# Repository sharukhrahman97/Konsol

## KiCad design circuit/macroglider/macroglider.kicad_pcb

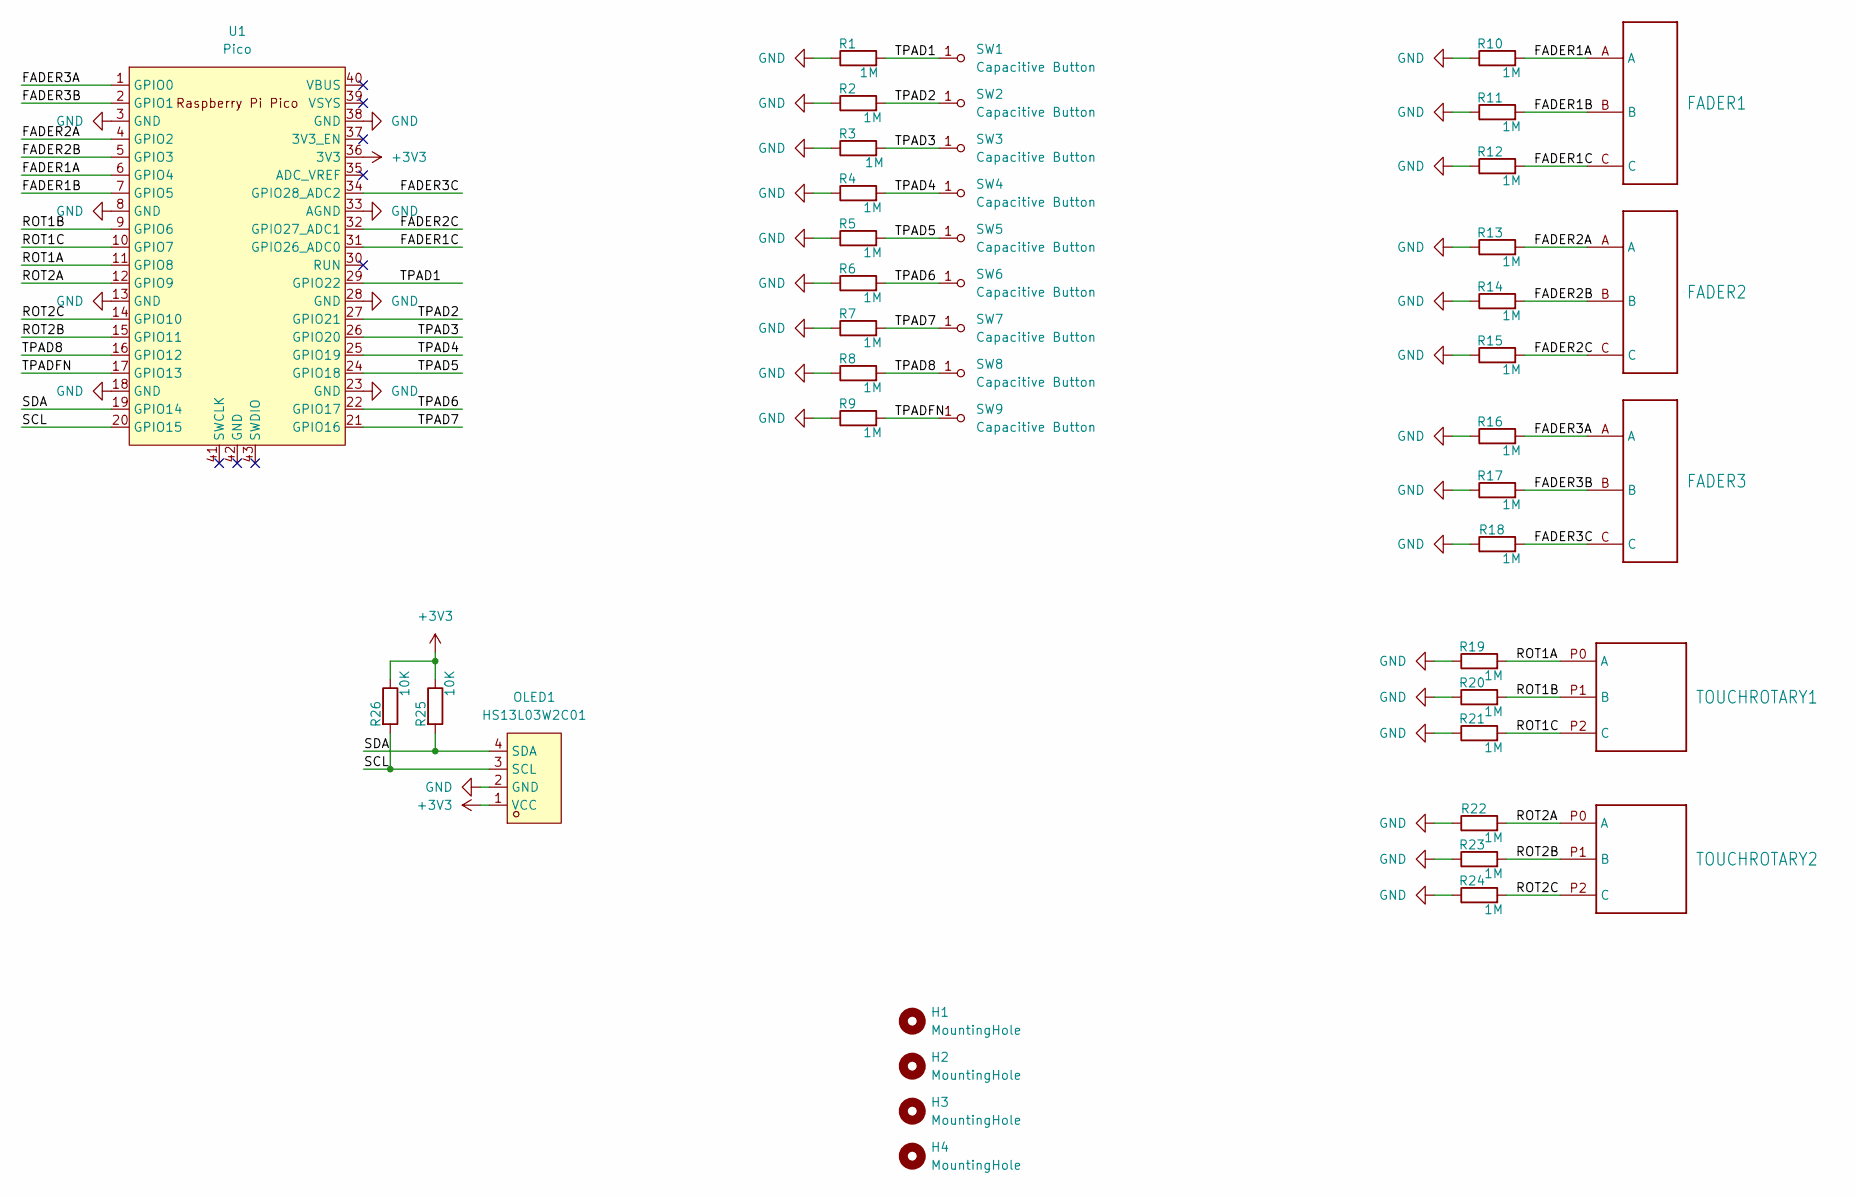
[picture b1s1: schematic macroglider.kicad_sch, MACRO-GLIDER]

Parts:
FADER1, FADER2, FADER3: TOUCHSLIDER3_8x40B
H1, H2, H3, H4: MountingHole; MountingHole_2.7mm_M2.5_ISO14580
OLED1: HS13L03W2C01; OLED-TH_L35.4-W33.5_HS13L03W2C01_without_mount_outline; LCSC Part C7465997
R1, R2, R3, R4, R5, R6, R7, R8, R9, R10, R11, R12, R13, R14, R15, R16, R17, R18, R19, R20, R21, R22, R23, R24: 1M; R_0603_1608Metric
R25, R26: 10K; R_0603_1608Metric
SW1, SW2, SW3, SW4, SW5, SW6, SW7, SW8, SW9: Capacitive Button; Pad-CapacitiveTouch
TOUCHROTARY1, TOUCHROTARY2: TOUCHROTARY1B
U1: Pico; RPi_Pico_SMD

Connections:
+3V3: OLED1.1 (VCC), R25.1, R26.1, U1.36 (3V3)
/FADER1A: FADER1.A, R10.2, U1.6 (GPIO4)
/FADER1B: FADER1.B, R11.2, U1.7 (GPIO5)
/FADER1C: FADER1.C, R12.2, U1.31 (GPIO26_ADC0)
/FADER2A: FADER2.A, R13.2, U1.4 (GPIO2)
/FADER2B: FADER2.B, R14.2, U1.5 (GPIO3)
/FADER2C: FADER2.C, R15.2, U1.32 (GPIO27_ADC1)
/FADER3A: FADER3.A, R16.2, U1.1 (GPIO0)
/FADER3B: FADER3.B, R17.2, U1.2 (GPIO1)
/FADER3C: FADER3.C, R18.2, U1.34 (GPIO28_ADC2)
/ROT1A: R19.2, TOUCHROTARY1.P0 (A), U1.11 (GPIO8)
/ROT1B: R20.2, TOUCHROTARY1.P1 (B), U1.9 (GPIO6)
/ROT1C: R21.2, TOUCHROTARY1.P2 (C), U1.10 (GPIO7)
/ROT2A: R22.2, TOUCHROTARY2.P0 (A), U1.12 (GPIO9)
/ROT2B: R23.2, TOUCHROTARY2.P1 (B), U1.15 (GPIO11)
/ROT2C: R24.2, TOUCHROTARY2.P2 (C), U1.14 (GPIO10)
/SCL: OLED1.3 (SCL), R26.2, U1.20 (GPIO15)
/SDA: OLED1.4 (SDA), R25.2, U1.19 (GPIO14)
/TPAD1: R1.2, SW1.1 (A), U1.29 (GPIO22)
/TPAD2: R2.2, SW2.1 (A), U1.27 (GPIO21)
/TPAD3: R3.2, SW3.1 (A), U1.26 (GPIO20)
/TPAD4: R4.2, SW4.1 (A), U1.25 (GPIO19)
/TPAD5: R5.2, SW5.1 (A), U1.24 (GPIO18)
/TPAD6: R6.2, SW6.1 (A), U1.22 (GPIO17)
/TPAD7: R7.2, SW7.1 (A), U1.21 (GPIO16)
/TPAD8: R8.2, SW8.1 (A), U1.16 (GPIO12)
/TPADFN: R9.2, SW9.1 (A), U1.17 (GPIO13)
GND: OLED1.2 (GND), R1.1, R2.1, R3.1, R4.1, R5.1, R6.1, R7.1, R8.1, R9.1, R10.1, R11.1, R12.1, R13.1, R14.1, R15.1, R16.1, R17.1, R18.1, R19.1, R20.1, R21.1, R22.1, R23.1, R24.1, U1.3 (GND), U1.8 (GND), U1.13 (GND), U1.18 (GND), U1.23 (GND), U1.28 (GND), U1.33 (AGND), U1.38 (GND)

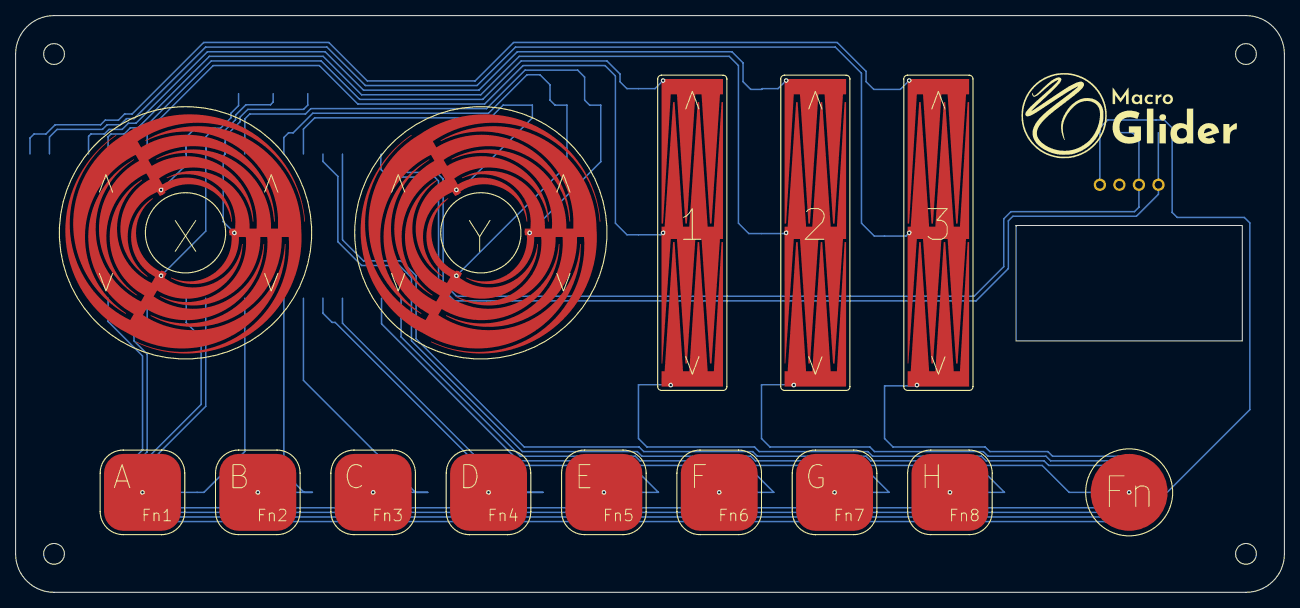
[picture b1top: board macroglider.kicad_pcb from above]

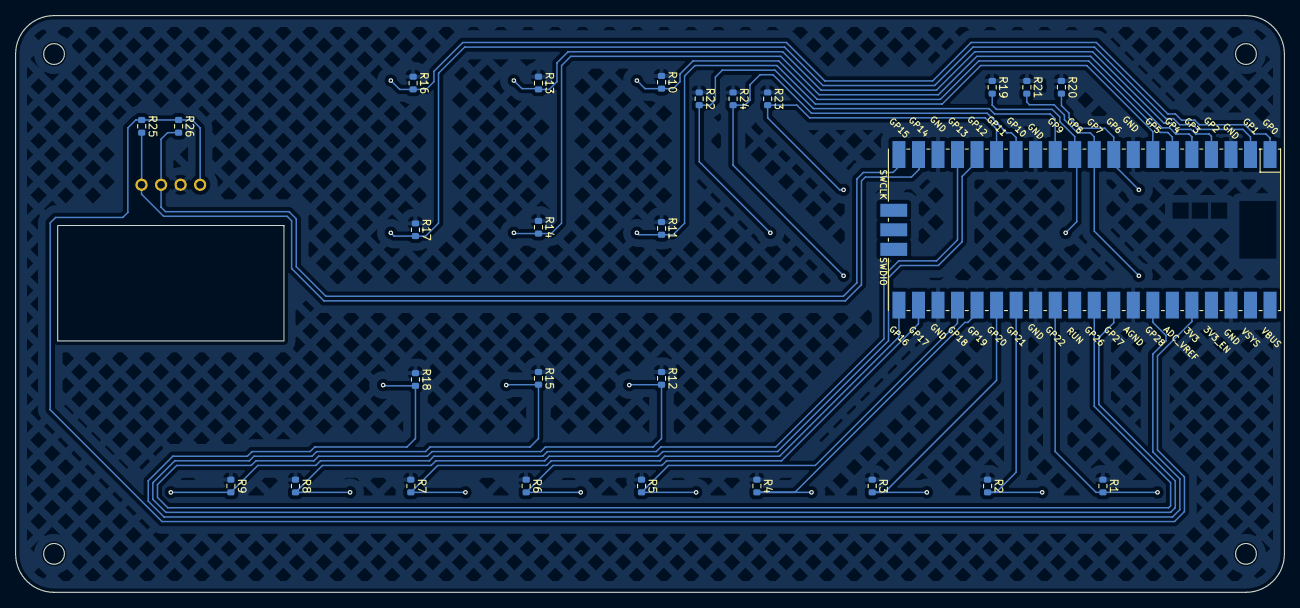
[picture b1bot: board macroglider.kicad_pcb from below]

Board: 2 copper layers, 165.0 x 75.0 mm, 46 parts (27 on the bottom side), 28 nets.

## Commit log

2024-04-30 init
2024-04-30 3d blender model
